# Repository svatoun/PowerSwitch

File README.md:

# PowerSwitch
Jednoduché udělátko, které spíná s prodlevou několik napájecích větví, aby se předešlo proudovému nárazu při zapnutí zařízení. Více informací viz [TT-Odbočná Wiki](http://cs.ttodbocna.wikia.com/wiki/PowerSwitch)

# PowerSwitch (English)
Simple device that power individual lines with a delay to reduce startup power peak. Sorry, more information in Czech language only (see above).

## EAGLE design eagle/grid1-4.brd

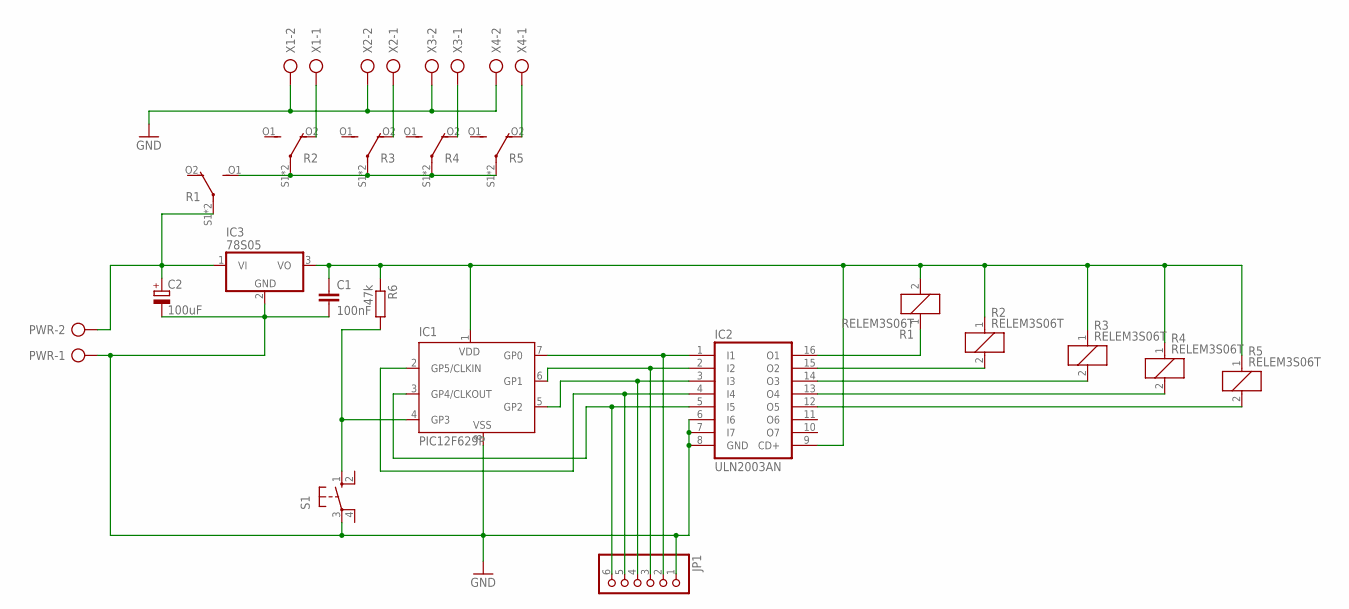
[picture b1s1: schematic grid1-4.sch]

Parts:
C1: 100nF; C050-025X075
C2: 100uF; E2,5-6
IC1: PIC12F629P; DIL8
IC2: ULN2003AN; DIL16
IC3: 78S05; TO220V
JP1: PINHD-1X6; 1X06
PWR: AK500/2
R1, R2, R3, R4, R5: RELEM3S06T; VIGAN
R6: 47k; 0207/10
S1: 10-XX; B3F-10XX
X1, X2, X3, X4: AK500/2

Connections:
GND: C1.2, C2.-, IC1.8 (VSS), IC2.6 (I6), IC2.7 (I7), IC2.8 (GND), IC3.2 (GND), JP1.1, PWR.1, S1.3, X1.2, X2.2, X3.2, X4.2
MASTER-PW: R1.O1 (O-ON), R2.S1, R2.S2, R3.S1, R3.S2, R4.S1, R4.S2, R5.S1, R5.S2
unnamed: IC1.7 (GP0), IC2.1 (I1), JP1.2
unnamed: IC1.6 (GP1), IC2.2 (I2), JP1.3
unnamed: IC1.5 (GP2), IC2.3 (I3), JP1.4
unnamed: IC1.3 (GP4/CLKOUT), IC2.5 (I5), JP1.6
unnamed: IC1.2 (GP5/CLKIN), IC2.4 (I4), JP1.5
unnamed: IC2.16 (O1), R1.1
unnamed: IC2.15 (O2), R2.2
unnamed: IC2.14 (O3), R3.2
unnamed: IC2.13 (O4), R4.2
unnamed: IC2.12 (O5), R5.2
unnamed: IC1.4 (GP3), R6.2, S1.1 (S)
unnamed: R2.O2 (O-OFF), X1.1
unnamed: R3.O2 (O-OFF), X2.1
unnamed: R4.O2 (O-OFF), X3.1
unnamed: R5.O2 (O-OFF), X4.1
POW: C2.+, IC3.1 (VI), PWR.2, R1.S1, R1.S2
VDD: C1.1, IC1.1 (VDD), IC2.9 (CD+), IC3.3 (VO), R1.2, R2.1, R3.1, R4.1, R5.1, R6.1

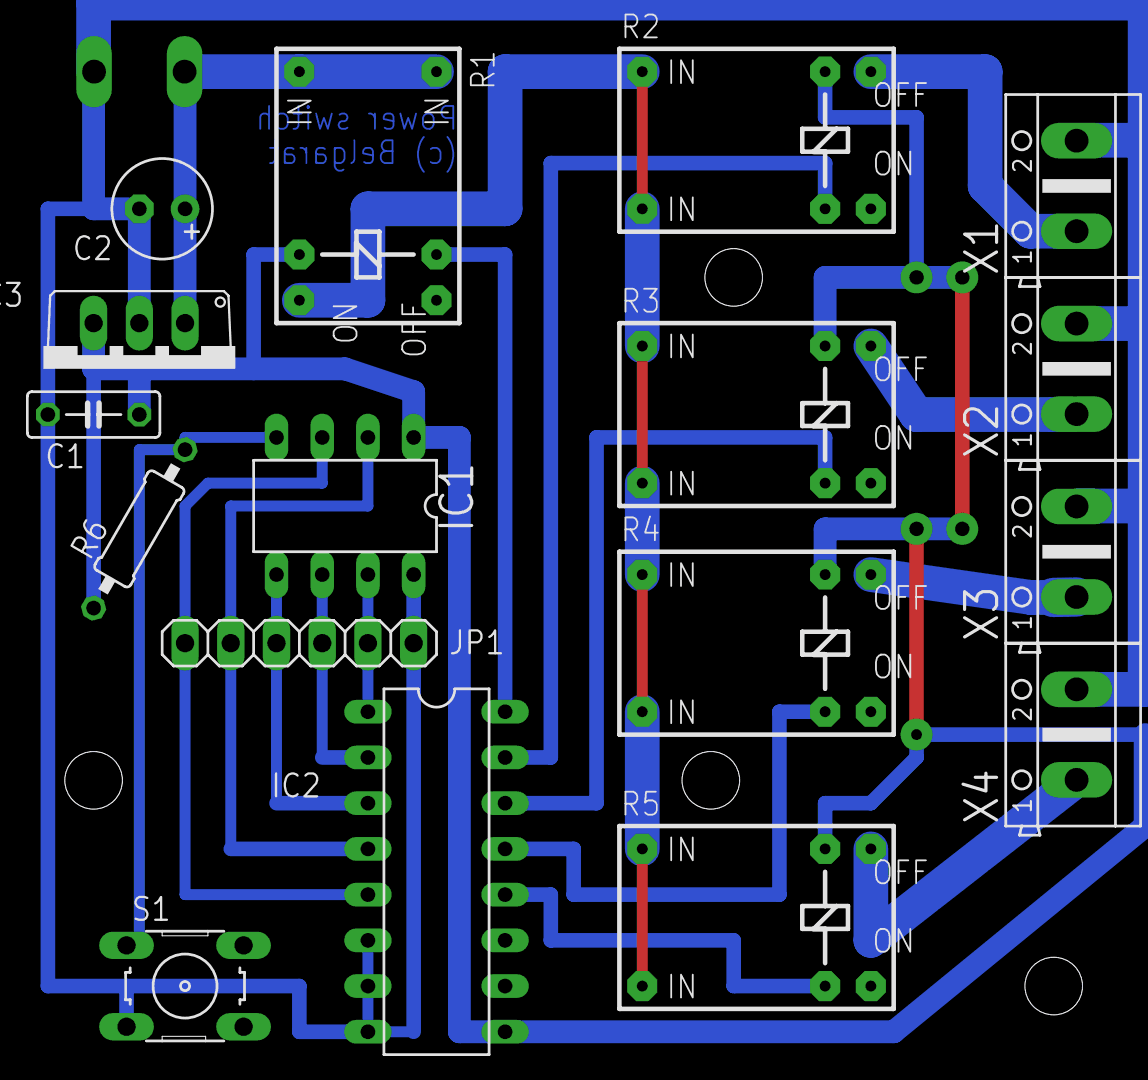
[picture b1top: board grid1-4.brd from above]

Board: 2 copper layers, 18 parts (1 on the bottom side), 19 nets.

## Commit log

2018-04-06 Eagle files added
2018-04-06 Readme updated
